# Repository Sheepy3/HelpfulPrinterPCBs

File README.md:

# HelpfulPrinterPCBs
Some PCBs I designed for my Ender3NG, which can be used on other printers too!
---
# Klipperscreen Riser

I designed this riser to use a 11-pin [ribboncable](https://www.aliexpress.us/item/3256805087347551.html?spm=a2g0o.order_list.order_list_main.16.5b981802oz6h32&gatewayAdapt=glo2usa) to rise a [small TFT](https://www.aliexpress.us/item/3256805467182919.html?spm=a2g0o.order_list.order_list_main.25.193f1802pya02f&gatewayAdapt=glo2usa) off my rasberry PI zero 2W. this allowed me to have the screen on the front of my priter and the raspberry pi in the back with the rest of the electronics. It also includes a switch for the backlight! [Here's the screenwiki page I found the pinout on.](http://www.lcdwiki.com/3.5inch_RPi_Display).

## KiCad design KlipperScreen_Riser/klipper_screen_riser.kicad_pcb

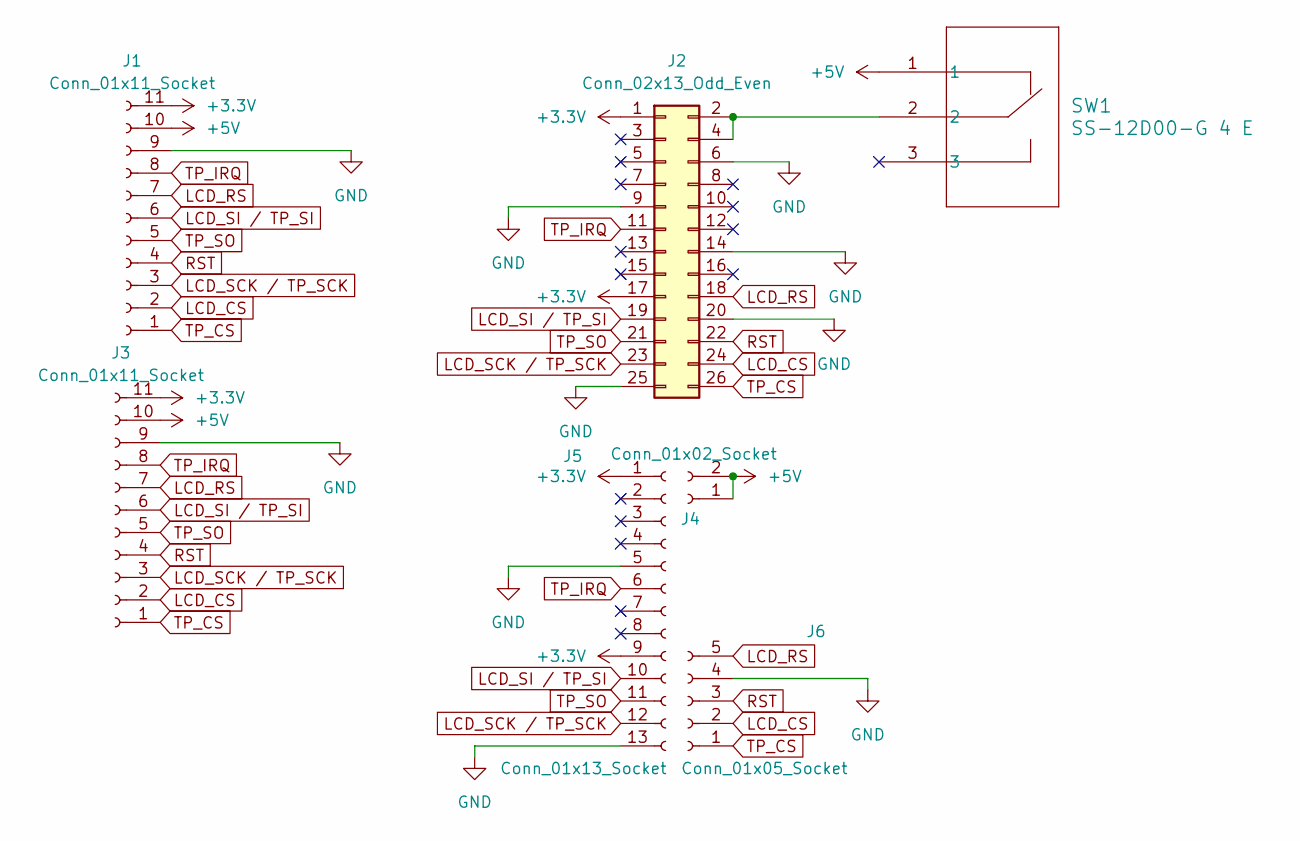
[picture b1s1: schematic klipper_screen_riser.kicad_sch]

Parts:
J1, J3: Conn_01x11_Socket; PinSocket_1x11_P2.54mm_Vertical
J2: Conn_02x13_Odd_Even; PinHeader_2x13_P2.54mm_Vertical
J4: Conn_01x02_Socket; PinSocket_1x02_P2.54mm_Vertical
J5: Conn_01x13_Socket; PinHeader_1x13_P2.54mm_Vertical
J6: Conn_01x05_Socket; PinSocket_1x05_P2.54mm_Vertical
SW1: SS-12D00-G 4 E; 1P2T_SS-12D00_CNK

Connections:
+3.3V: J1.11, J2.1, J2.17, J3.11, J5.1, J5.9
+5V: J1.10, J3.10, J4.1, J4.2, SW1.1
GND: J1.9, J2.6, J2.9, J2.14, J2.20, J2.25, J3.9, J5.5, J5.13, J6.4
LCD_CS: J1.2, J2.24, J3.2, J6.2
LCD_RS: J1.7, J2.18, J3.7, J6.5
LCD_SCK / TP_SCK: J1.3, J2.23, J3.3, J5.12
LCD_SI / TP_SI: J1.6, J2.19, J3.6, J5.10
unnamed: J2.2, J2.4, SW1.2
RST: J1.4, J2.22, J3.4, J6.3
TP_CS: J1.1, J2.26, J3.1, J6.1
TP_IRQ: J1.8, J2.11, J3.8, J5.6
TP_SO: J1.5, J2.21, J3.5, J5.11

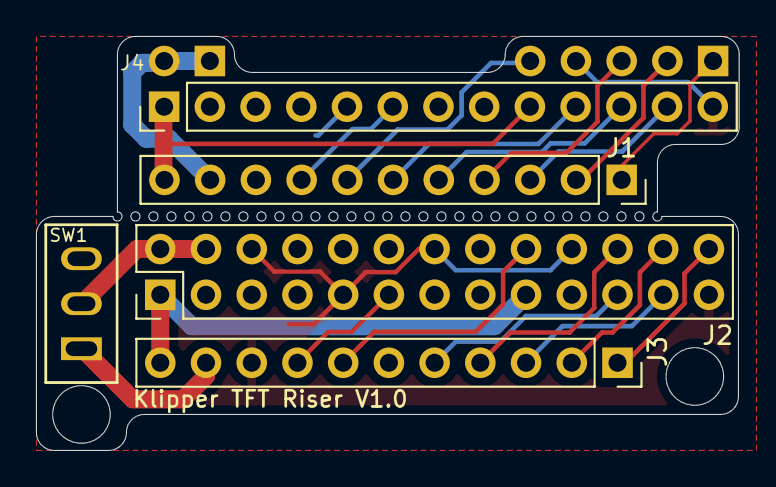
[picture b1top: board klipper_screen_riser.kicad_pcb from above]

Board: 2 copper layers, 39.0 x 23.0 mm, 7 parts (0 on the bottom side), 12 nets.

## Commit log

2024-12-23 KlipperScreen Riser
